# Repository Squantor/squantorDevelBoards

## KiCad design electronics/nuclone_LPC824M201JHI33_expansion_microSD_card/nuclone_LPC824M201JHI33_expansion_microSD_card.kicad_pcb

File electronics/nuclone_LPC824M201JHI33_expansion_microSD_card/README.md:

# LPC824M201JHI33 nuclone shrunk expansion board with micro SD card socket
Small nuclone expansion board for the [LPC824 nuclone](https://github.com/Squantor/squantorDevelBoards/tree/master/hardware/nuclone_LPC824M201JHI33/README.md) with a micro SD card socket and a 4 pin JST connection for hooking up an UART. The goal of this board to play around with a SD card driver not using SPI mode. Will focus first on single data line SD and later on switching to two and four dataline SD.
## Debug connector
There is a connector present to hook up a logic analyser for checking the signals.
# HSI (Hardware Software Interface)
This applies to a project that has a embedded software component. Describe what each pin/bus does, what it is connected to, what its function is and some "safe" behaviour when starting up.
* LPC824 PIO24 is connected to UART TX via 100Ohm series resistor
* LPC824 PIO25 is connected to UART RX via 100Ohm series resistor
* LPC824 PIO12 is connected to LED0 via 4.7KOhm resistor, this is used as alive blinky indicator
* LPC824 PIO23 is connected to LED1 via 4.7KOhm resistor, this is used as an activity indicator
* TODO SD card connections
## TODO's
Still some things need to be done:
* schematic entry
* PCB layout
* Review with one night in between
* Produce at [OSHPARK](https://oshpark.com/)
* Assemble
* Test & characterise
* update Readme.md with pictures and BOM
## BOM
* Any 25 style 8 pin SOIC serial flash is suitable like the [Winbond W25X20CLSNIG](https://lcsc.com/product-detail/FLASH_Winbond-Elec-W25X20CLSNIG_C34591.html)

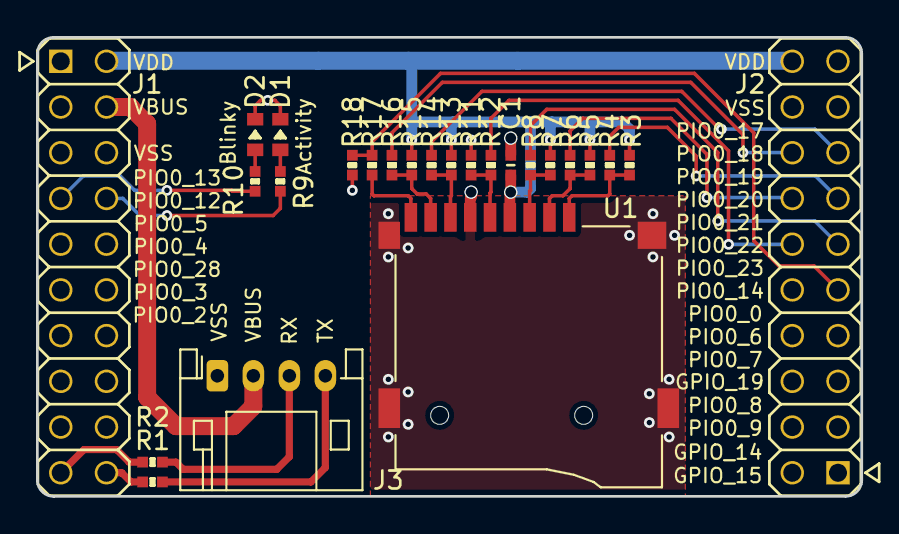
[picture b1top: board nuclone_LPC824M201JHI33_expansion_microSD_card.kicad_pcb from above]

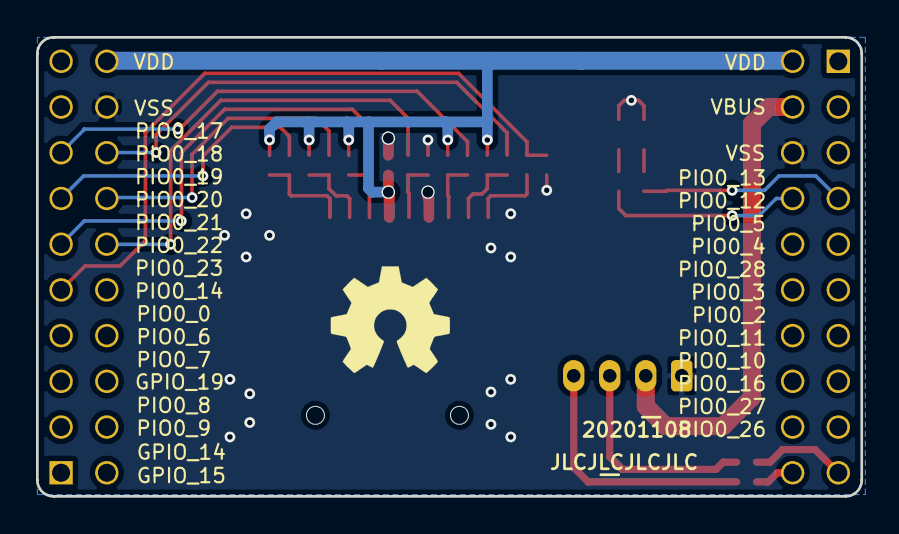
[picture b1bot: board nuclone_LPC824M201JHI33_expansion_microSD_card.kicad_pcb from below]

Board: 2 copper layers, 45.8 x 25.5 mm, 28 parts (3 on the bottom side), 25 nets.

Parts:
C1: 1u; C_0402
D1, D2: LED; LED_0603_hand
J1: nuclone_small_left; Header-0254-2X10-H010
J2: nuclone_small_right; Header-0254-2X10-H010
J3: DevBoardUartInput; JST_PH_S4B-PH-K_1x04_P2.00mm_Horizontal
N1: OHWLOGO; OSHW-Symbol_6.7x6mm_SilkScreen
N2: 20201108; Label_Generic
N3: JLCJLCJLCJLC; Label_Generic
R1, R2, R4, R6, R8, R12, R14, R16, R17: 100; R_0402_hand
R3, R5, R7, R11, R13, R15: 10k; R_0402_hand
R9, R10: 4.7K; R_0402_hand
R18: 100k; R_0402_hand
U1: microSD_socket; SDmicro_XUNPU_TF-115

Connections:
/CLK: J2.12, R12.2
/CMD: J2.11, R8.2
/CardDet: J2.9, R17.2, R18.2
/DAT0: J2.15, R14.2
/DAT1: J2.16, R16.2
/DAT2: J2.13, R4.2
/DAT3: J2.14, R6.2
/LED0: J1.8, R9.2
/LED1: J1.7, R10.2
/UART_RX: J1.19, R1.1
/UART_TX: J1.20, R2.1
/VBUS: J1.4, J3.2
/VDD: C1.1, J1.1, J1.2, J2.20, R3.2, R5.2, R7.2, R13.2, R15.2, U1.4
/VSS: C1.2, D1.1, D2.1, J1.6, J2.18, J3.1, R11.2, R18.1, U1.6, U1.S
unnamed: D1.2, R9.1
unnamed: D2.2, R10.1
unnamed: J3.3, R1.2
unnamed: J3.4, R2.2
unnamed: R3.1, R4.1, U1.1
unnamed: R5.1, R6.1, U1.2
unnamed: R7.1, R8.1, U1.3
unnamed: R11.1, R12.1, U1.5
unnamed: R13.1, R14.1, U1.7
unnamed: R15.1, R16.1, U1.8
unnamed: R17.1, U1.CD

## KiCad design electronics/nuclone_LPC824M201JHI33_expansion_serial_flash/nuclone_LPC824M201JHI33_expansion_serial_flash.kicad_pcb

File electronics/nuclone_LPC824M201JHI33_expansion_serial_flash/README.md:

# LPC824M201JHI33 nuclone shrunk expansion board with serial flash
Small nuclone expansion board for the [LPC824 nuclone](https://github.com/Squantor/squantorDevelBoards/tree/master/hardware/nuclone_LPC824M201JHI33/README.md) that also has a serial flash and a 4 pin JST connection for hooking up an UART. The goal of this board to play around with efficient serial flash handling, SPI drivers and filesystem driver development. Lets see if we can wring some performance out of it with QSPI.
# HSI (Hardware Software Interface)
This applies to a project that has a embedded software component. Describe what each pin/bus does, what it is connected to, what its function is and some "safe" behaviour when starting up.
* UART connection
* SPI connection
* blinking led for alive?
## TODO's
Still some things need to be done:
* schematic entry 
* PCB layout
* Review with one night in between
* Produce at [OSHPARK](https://oshpark.com/)
* Assemble
* Test & characterise
* update Readme.md with pictures and BOM
## BOM
* Any 25 style 8 pin SOIC serial flash is suitable like the [Winbond W25X20CLSNIG](https://lcsc.com/product-detail/FLASH_Winbond-Elec-W25X20CLSNIG_C34591.html)

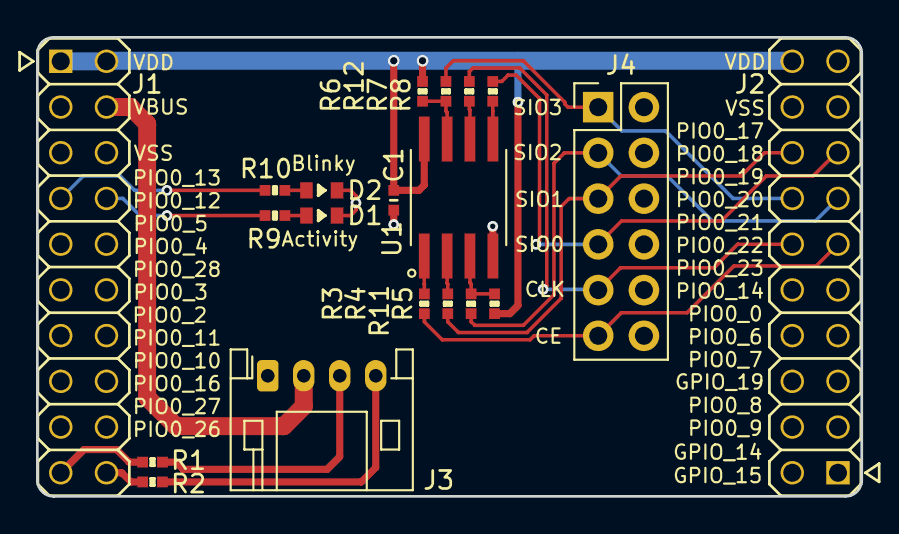
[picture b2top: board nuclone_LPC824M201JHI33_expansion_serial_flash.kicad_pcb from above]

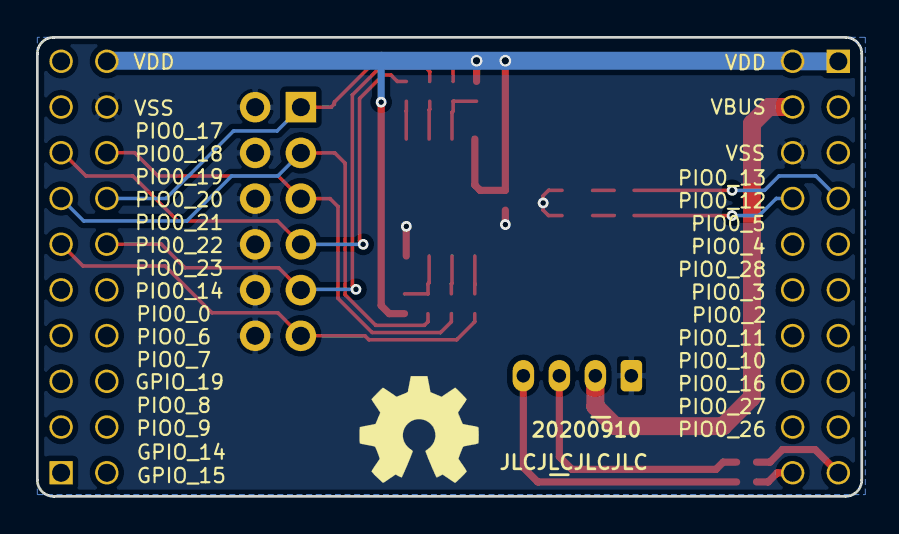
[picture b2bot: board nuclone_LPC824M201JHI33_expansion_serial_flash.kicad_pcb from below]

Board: 2 copper layers, 45.8 x 25.5 mm, 23 parts (3 on the bottom side), 23 nets.

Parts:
C1: 1u; C_0402
D1, D2: LED; LED_0603_hand
J1: nuclone_small_left; Header-0254-2X10-H010
J2: nuclone_small_right; Header-0254-2X10-H010
J3: DevBoardUartInput; JST_PH_S4B-PH-K_1x04_P2.00mm_Horizontal
J4: Conn_02x06_Odd_Even; PinHeader_2x06_P2.54mm_Vertical
N1: OHWLOGO; OSHW-Symbol_6.7x6mm_SilkScreen
N2: 20200910; Label_Generic
N3: JLCJLCJLCJLC; Label_Generic
R1, R2, R3, R4, R7, R8, R11, R12: 100; R_0402_hand
R5, R6: 10k; R_0402_hand
R9, R10: 4.7K; R_0402_hand
U1: generic 25XNN serial flash; SOIC-8_dual_wide

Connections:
/CE_FLASH: J2.11, J4.11, R3.2
/CLK: J2.12, J4.9, R7.1
/LED0: J1.8, R9.2
/LED1: J1.7, R10.2
/SIO0: J2.15, J4.7, R8.1
/SIO1: J2.16, J4.5, R4.2
/SIO2: J2.13, J4.3, R11.2
/SIO3: J2.14, J4.1, R12.1
/UART_RX: J1.19, R1.1
/UART_TX: J1.20, R2.1
/VBUS: J1.4, J3.2
/VDD: C1.1, J1.1, J1.2, J2.20, R5.2, R6.1, U1.8
/VSS: C1.2, D1.1, D2.1, J1.6, J2.18, J3.1, J4.2, J4.4, J4.6, J4.8, J4.10, J4.12, U1.4
unnamed: D1.2, R9.1
unnamed: D2.2, R10.1
unnamed: J3.3, R1.2
unnamed: J3.4, R2.2
unnamed: R3.1, U1.1
unnamed: R4.1, U1.2
unnamed: R7.2, U1.6
unnamed: R8.2, U1.5
unnamed: R5.1, R11.1, U1.3
unnamed: R6.2, R12.2, U1.7

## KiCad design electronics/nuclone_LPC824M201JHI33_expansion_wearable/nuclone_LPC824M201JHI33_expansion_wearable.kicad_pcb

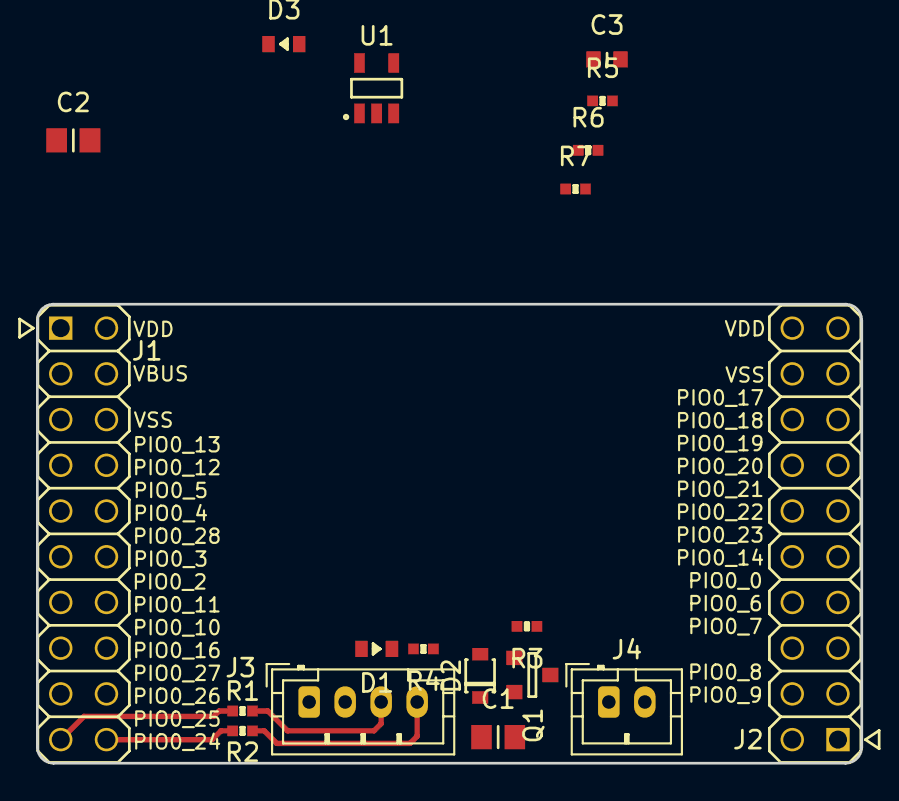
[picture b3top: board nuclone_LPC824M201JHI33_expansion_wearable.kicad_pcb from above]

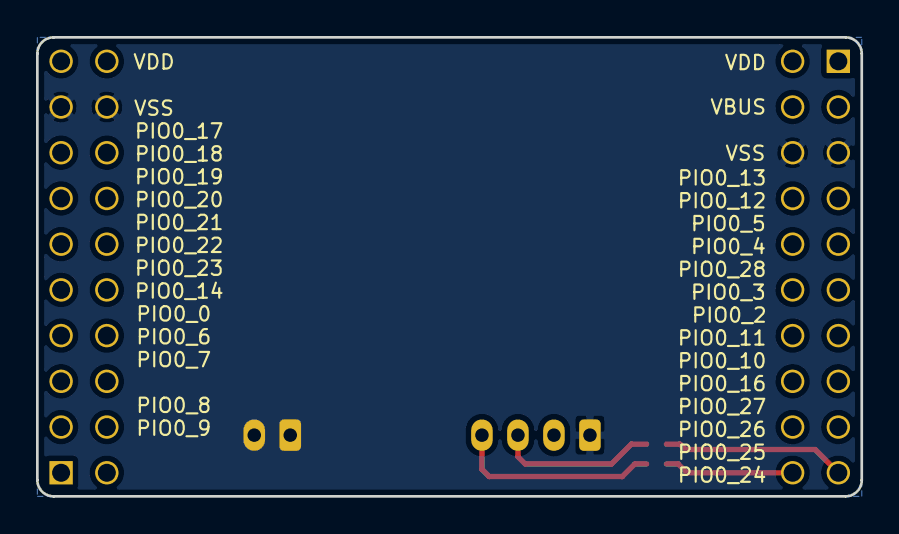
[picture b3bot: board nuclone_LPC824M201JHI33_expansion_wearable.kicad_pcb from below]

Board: 2 copper layers, 45.8 x 25.5 mm, 22 parts (3 on the bottom side), 13 nets.

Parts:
C1, C2: 10u; C_0805+0603
C3: 1u; C_0603
D1: GRN; LED_0603_hand
D2: NSR0320; SOD_323_onsemi
D3: RED; LED_0603_hand
J1: nuclone_small_left; Header-0254-2X10-H010
J2: nuclone_small_right; Header-0254-2X10-H010
J3: DevBoardUartInput; JST_PH_B4B-PH-K_1x04_P2.00mm_Vertical
J4: batt_recharge; JST_PH_B2B-PH-K_1x02_P2.00mm_Vertical
N1: OHWLOGO; OSHW-Symbol_6.7x6mm_SilkScreen
N2: 20200910; Label_Generic
N3: JLCJLCJLCJLC; Label_Generic
Q1: DMG2305; SOT23-3
R1, R2: 100; R_0402_hand
R3: 100K; R_0402_hand
R4, R6: 1K; R_0402_hand
R5: 22K; R_0402_hand
R7: 47K; R_0402_hand
U1: MCP738312-OT; SOT23-5-Microchip-OT

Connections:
/PIO0_24: J1.20, R2.1
/PIO0_25: J1.19, R1.1
/VBAT: C2.1, J4.1, Q1.3, U1.3
/VBUS: C1.1, D2.1, J1.3, J1.4, Q1.2
/VDD: J1.1, J1.2, J2.19, J2.20, R7.2
/VSS: C1.2, C2.2, C3.1, J1.5, J1.6, J2.17, J2.18, J3.1, J4.2, R3.1, R4.1, R5.2, U1.2
/VUSB: C3.2, D1.2, D2.2, D3.2, J3.2, Q1.1, R3.2, U1.4
/chrg_en: R5.1, U1.5
/chrg_state: R6.1, R7.1, U1.1
unnamed: D1.1, R4.2
unnamed: D3.1, R6.2
unnamed: J3.3, R1.2
unnamed: J3.4, R2.2

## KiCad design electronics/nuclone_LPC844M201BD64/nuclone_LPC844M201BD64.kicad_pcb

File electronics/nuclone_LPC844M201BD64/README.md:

# Nuclone development board for the LPC84XM201BD64
Development board for the LPC844 and LPC845 in TQFP64 package.
# HSI (Hardware Software Interface)
* TODO pins
* The crystal is a 12MHz 3225 type
* VREFP is connected to VDDA via default closed jumper labeled VREFP
* VREFN is connected to VSSA via default closed jumper labeled VREFN
## TODO's
Still some things need to be done:
* Schematic
* Layout
* review with one night in between
* Produce at [OSHPARK](https://oshpark.com/)
* Assemble
* Test & characterise
* update Readme.md with pictures and BOM
## BOM

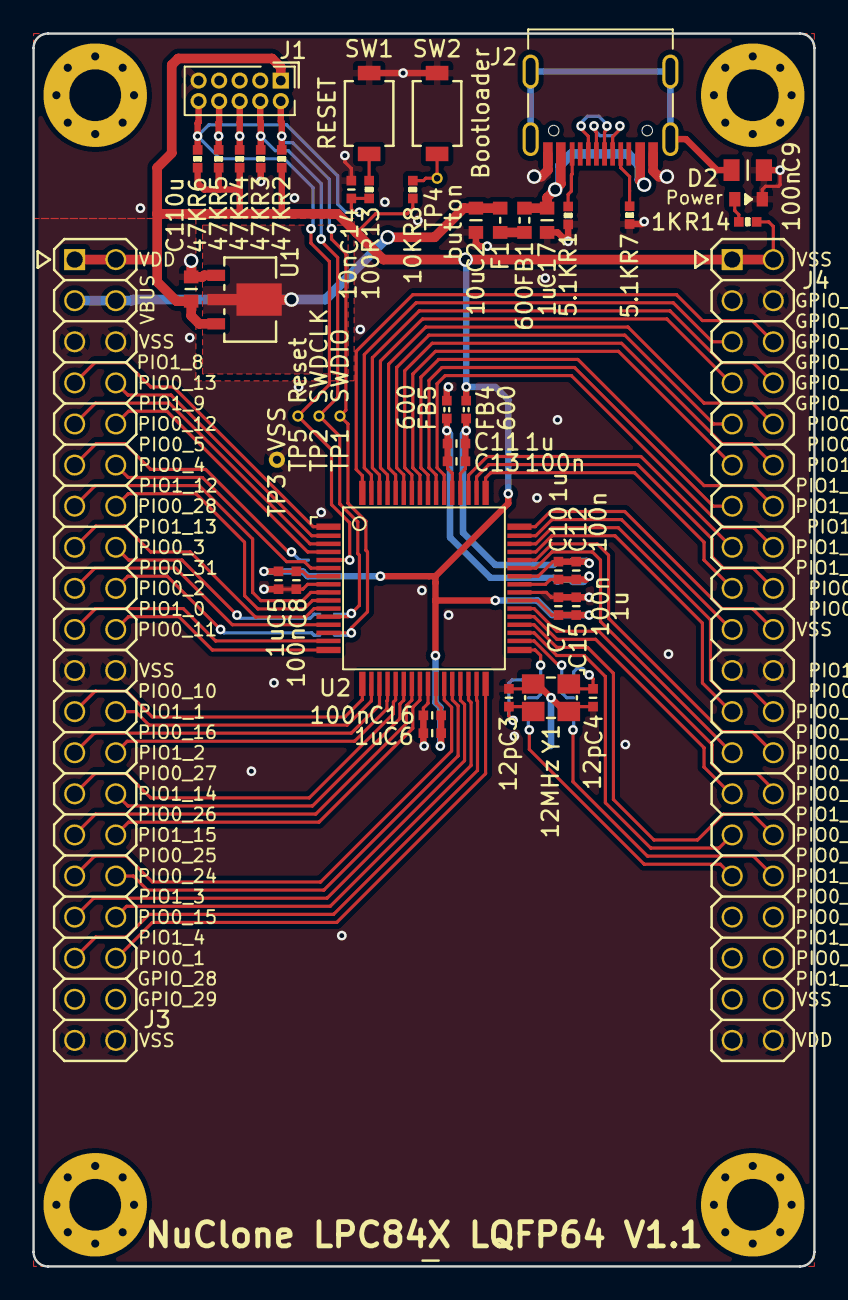
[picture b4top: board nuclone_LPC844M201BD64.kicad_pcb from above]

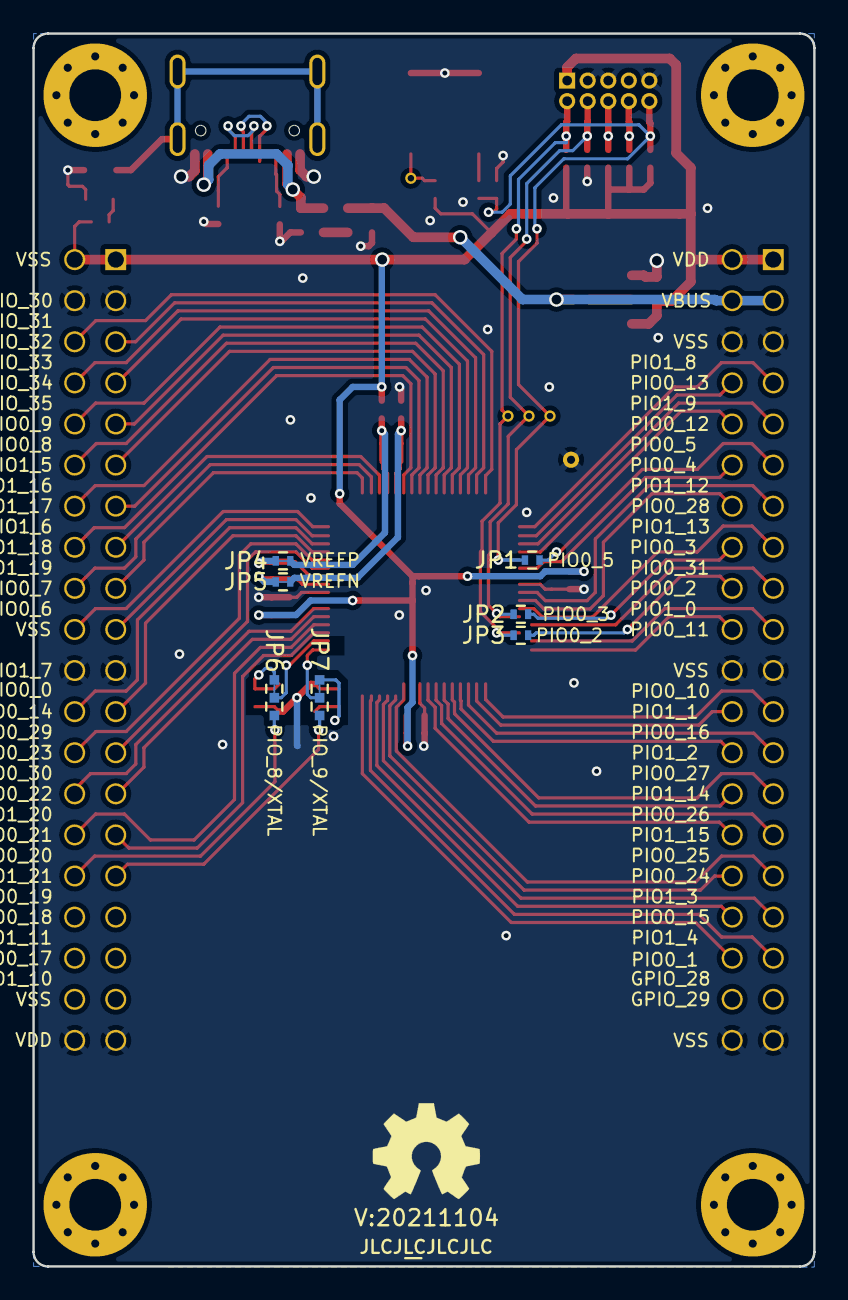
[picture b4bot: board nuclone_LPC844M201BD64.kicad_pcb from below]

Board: 2 copper layers, 48.3 x 76.2 mm, 61 parts (10 on the bottom side), 80 nets.

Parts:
C1, C2: 10u; C_0603
C3, C4: 12p; C_0402
C5, C6, C10, C11, C15: 1u; C_0402
C7, C8, C12, C13, C16: 100n; C_0402
C9: 100n; C_0805
C14: 10n; C_0402
C17: 1u; C_0603
D2: GREEN; LED_0603_hand
F1: 0.5A; F_0603_hand
FB1: 600; L_0603
FB4, FB5: 600; L_0402
H1, H2, H3, H4: MountingHole; MountingHole_3.2mm_M3_Pad_Via
J1: JTAG_2X05; Header-0127-2X05-H006
J2: TYPE-C-31-M-12; USB-C-HRO-31-M-12
J3: nuclone_small_left; nuclone_medium_left
J4: nuclone_small_right; nuclone_medium_right
JP1: PIO0_5; solder_jumper_2way_noconn
JP2: PIO0_3; solder_jumper_2way_noconn
JP3: PIO0_2; solder_jumper_2way_noconn
JP4: VREFP; solder_jumper_2way_conn
JP5: VREFN; solder_jumper_2way_conn
JP6: PIO_8/XTAL; solder_jumper_3way_12conn
JP7: PIO_9/XTAL; solder_jumper_3way_12conn
N1: OHWLOGO; OSHW-Symbol_6.7x6mm_SilkScreen
N2: 20211104; Label_version
N3: JLCJLCJLCJLC; Label_Generic
N4: NuClone LPC84X LQFP64 V1.1; Label_Generic
R1, R7: 5.1K; R_0402_hand
R2, R3, R4, R5, R6: 47K; R_0402_hand
R8: 10K; R_0402_hand
R13: 100; R_0402_hand
R14: 1K; R_0402_hand
SW1: RESET; TD-85XU
SW2: Bootloader; TD-85XU
TP1: SWDIO; TestPoint_hole_H04R07
TP2: SWDCLK; TestPoint_hole_H04R07
TP3: VSS; TestPoint_hole_H05R10
TP4: button; TestPoint_hole_H04R07
TP5: Reset; TestPoint_hole_H04R07
U1: MCP1702-MB; SOT89-NXP
U2: LPC845M301BD64; SOT314-2
Y1: 12MHz; Crystal_3225_4

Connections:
/Bootloader: R8.1, SW2.2, TP4.1
/PIO0_0: J4.20 (VSS), U2.48 (PIO0_0/ACMP_I1/TDO)
/PIO0_1: J3.36 (GPIO_27), U2.32 (PIO0_1/ACMP_I2/CLKIN/TDI)
/PIO0_2: J3.18 (GPIO_11), JP3.1
/PIO0_3: J3.16 (GPIO_09), JP2.1
/PIO0_4: J3.12 (GPIO_05), U2.6 (PIO0_4/ADC_11/TRSTN/WAKEUP)
/PIO0_5: J3.11 (GPIO_04), JP1.1
/PIO0_6: J4.24 (GPIO_48), U2.46 (PIO0_6/ADC_1/ACMPVREF)
/PIO0_7: J4.23 (GPIO_49), U2.45 (PIO0_7/ADC_0)
/PIO0_8: J4.32 (GPIO_56), JP6.3
/PIO0_8_I: JP6.2, U2.34 (PIO0_8/XTALIN)
/PIO0_9: J4.31 (GPIO_57), JP7.3
/PIO0_9_I: JP7.2, U2.33 (PIO0_9/XTALOUT)
/PIO0_10: J3.23 (GPIO_14), U2.17 (PIO0_10/I2C0_SCL_)
/PIO0_11: J3.20 (GPIO_13), U2.16 (PIO0_11/I2C0_SDA)
/PIO0_12: J3.10 (GPIO_03), U2.4 (PIO0_12)
/PIO0_13: J3.8 (GPIO_01), U2.2 (PIO0_13/ADC_10)
/PIO0_14: J4.17 (GPIO_45), U2.49 (PIO0_14/ACMP_I3/ADC_2)
/PIO0_15: J3.34 (GPIO_25), U2.30 (PIO0_15)
/PIO0_16: J3.25 (GPIO_16), U2.19 (PIO0_16)
/PIO0_17: J4.5 (GPIO_33), U2.63 (PIO0_17/ADC_9/DACOUT_0)
/PIO0_18: J4.7 (GPIO_35), U2.61 (PIO0_18/ADC_8)
/PIO0_19: J4.10 (GPIO_36), U2.60 (PIO0_19/ADC_7)
/PIO0_20: J4.12 (GPIO_38), U2.58 (PIO0_20/ADC_6)
/PIO0_21: J4.11 (GPIO_39), U2.57 (PIO0_21/ADC_5)
/PIO0_22: J4.13 (GPIO_41), U2.55 (PIO0_22/ADC_4)
/PIO0_23: J4.15 (GPIO_43), U2.51 (PIO0_23/ADC_3/ACMP_I4)
/PIO0_24: J3.32 (GPIO_23), U2.28 (PIO0_24)
/PIO0_25: J3.31 (GPIO_22), U2.27 (PIO0_25)
/PIO0_26: J3.29 (GPIO_20), U2.23 (PIO0_26)
/PIO0_27: J3.27 (GPIO_18), U2.21 (PIO0_27)
/PIO0_28: J3.14 (GPIO_07), U2.10 (PIO0_28/WKTCLKIN)
/PIO0_29: J4.18 (GPIO_44), U2.50 (PIO0_29/_DACOUT_1)
/PIO0_30: J4.16 (GPIO_42), U2.54 (PIO0_30/ACMP_I5)
/PIO0_31: J3.17 (GPIO_10), U2.13 (PIO0_31/CAPT_X0)
/PIO1_0: J3.19 (GPIO_12), U2.15 (PIO1_0/CAPT_X1)
/PIO1_1: J3.24 (GPIO_15), U2.18 (PIO1_1/CAPT_X2)
/PIO1_2: J3.26 (GPIO_17), U2.20 (PIO1_2/CAPT_X3)
/PIO1_3: J3.33 (GPIO_24), U2.29 (PIO1_3/CAPT_X4)
/PIO1_4: J3.35 (GPIO_26), U2.31 (PIO1_4/CAPT_X5)
/PIO1_5: J4.29 (GPIO_55), U2.35 (PIO1_5/CAPT_X6)
/PIO1_6: J4.28 (GPIO_52), U2.38 (PIO1_6/CAPT_X7)
/PIO1_7: J4.19 (VSS), U2.47 (PIO1_7/CAPT_X8)
/PIO1_8: J3.7 (GPIO_00), U2.1 (PIO1_8/CAPT_YL)
/PIO1_9: J3.9 (GPIO_02), U2.3 (PIO1_9/CAPT_YH)
/PIO1_10: J4.6 (GPIO_32), U2.64 (PIO1_10)
/PIO1_11: J4.8 (GPIO_34), U2.62 (PIO1_11)
/PIO1_12: J3.13 (GPIO_06), U2.9 (PIO1_12)
/PIO1_13: J3.15 (GPIO_08), U2.11 (PIO1_13)
/PIO1_14: J3.28 (GPIO_19), U2.22 (PIO1_14)
/PIO1_15: J3.30 (GPIO_21), U2.24 (PIO1_15)
/PIO1_16: J4.30 (GPIO_54), U2.36 (PIO1_16)
/PIO1_17: J4.27 (GPIO_53), U2.37 (PIO1_17)
/PIO1_18: J4.25 (GPIO_51), U2.43 (PIO1_18)
/PIO1_19: J4.26 (GPIO_50), U2.44 (PIO1_19)
/PIO1_20: J4.14 (GPIO_40), U2.56 (PIO1_20)
/PIO1_21: J4.9 (GPIO_37), U2.59 (PIO1_21)
/RESET: C14.2, J1.10 (nRESET), JP1.2, R6.1, R13.1, TP5.1, U2.5 (RESET/PIO0_5)
/TCK: J1.4 (SWDCLK/TCK), JP2.2, R3.1, TP2.1, U2.12 (SWCLK/PIO0_3/TCK)
/TDI: J1.8 (TDI), R5.1
/TDO: J1.6 (SWO/TDO), R4.1
/TMS: J1.2 (SWDIO/TMS), JP3.2, R2.1, TP1.1, U2.14 (SWDIO/PIO0_2/TMS)
/VBUS: C2.2, F1.1, J3.3 (VBUS), J3.4 (VBUS), U1.2 (Vin)
/VDD: C1.1, C5.1, C6.1, C7.1, C8.1, C15.1, C16.1, FB4.2, J1.1 (VCC), J3.1 (VDD), J3.2 (VDD), J4.1 (VSS), J4.2 (VSS), R2.2, R4.2, R5.2, R6.2, R8.2, R14.2, U1.3 (Vout), U2.7 (VDD), U2.26 (VDD), U2.39 (VDD)
/VDDA: C11.1, C13.1, FB4.1, JP4.1, U2.52 (VDDA)
/VREFN: C10.2, C12.2, JP5.2, U2.41 (VREFN)
/VREFP: C10.1, C12.1, JP4.2, U2.42 (VREFP)
/VSS: C1.2, C2.1, C3.2, C4.2, C5.2, C6.2, C7.2, C8.2, C9.1, C14.1, C15.2, C16.2, C17.1, D2.1 (K), FB5.2, J1.3 (GND), J1.5 (GND), J1.9 (GNDDET), J2.A1B12 (GND), J2.B1A12 (GND), J3.5 (VSS), J3.6 (VSS), J3.21 (VSS), J3.22 (VSS), J3.39 (VSS), J3.40 (VSS), J4.3 (GPIO_31), J4.4 (GPIO_30), J4.21 (GPIO_47), J4.22 (GPIO_46), J4.39 (VDD), J4.40 (VDD), R1.1, R3.2, R7.1, SW1.1, SW2.1, TP3.1, U1.1 (GND), U2.8 (VSS), U2.25 (VSS), U2.40 (VSS), Y1.2, Y1.4
/VSSA: C11.2, C13.2, FB5.1, JP5.1, U2.53 (VSSA)
/XTALIN: C4.1, JP6.1, Y1.1
/XTALOUT: C3.1, JP7.1, Y1.3
unnamed: C9.2, J2.S (Shield)
unnamed: C17.2, FB1.2, J2.A4B9 (VBUS), J2.B4A9 (VBUS)
unnamed: D2.2 (A), R14.1
unnamed: F1.2, FB1.1
unnamed: J2.A5 (CC1), R7.2
unnamed: J2.A6 (DP1), J2.B6 (DP2)
unnamed: J2.A7 (DN1), J2.B7 (DN2)
unnamed: J2.B5 (CC2), R1.2
unnamed: R13.2, SW1.2

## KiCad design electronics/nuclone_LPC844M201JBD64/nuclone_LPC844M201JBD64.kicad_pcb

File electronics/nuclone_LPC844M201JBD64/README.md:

# Nuclone development board for the LPC844M201JBD64
Development board for the LPC844 in PQFP64 package.
# HSI (Hardware Software Interface)
* TODO pins
* The crystal is a 12MHz 3225 type
* VREFP is connected to VDDA via default closed jumper labeled VREFP
* VREFN is connected to VSSA via default closed jumper labeled VREFN
## TODO's
Still some things need to be done:
* Schematic
* Layout
* review with one night in between
* Produce at [OSHPARK](https://oshpark.com/)
* Assemble
* Test & characterise
* update Readme.md with pictures and BOM
## BOM

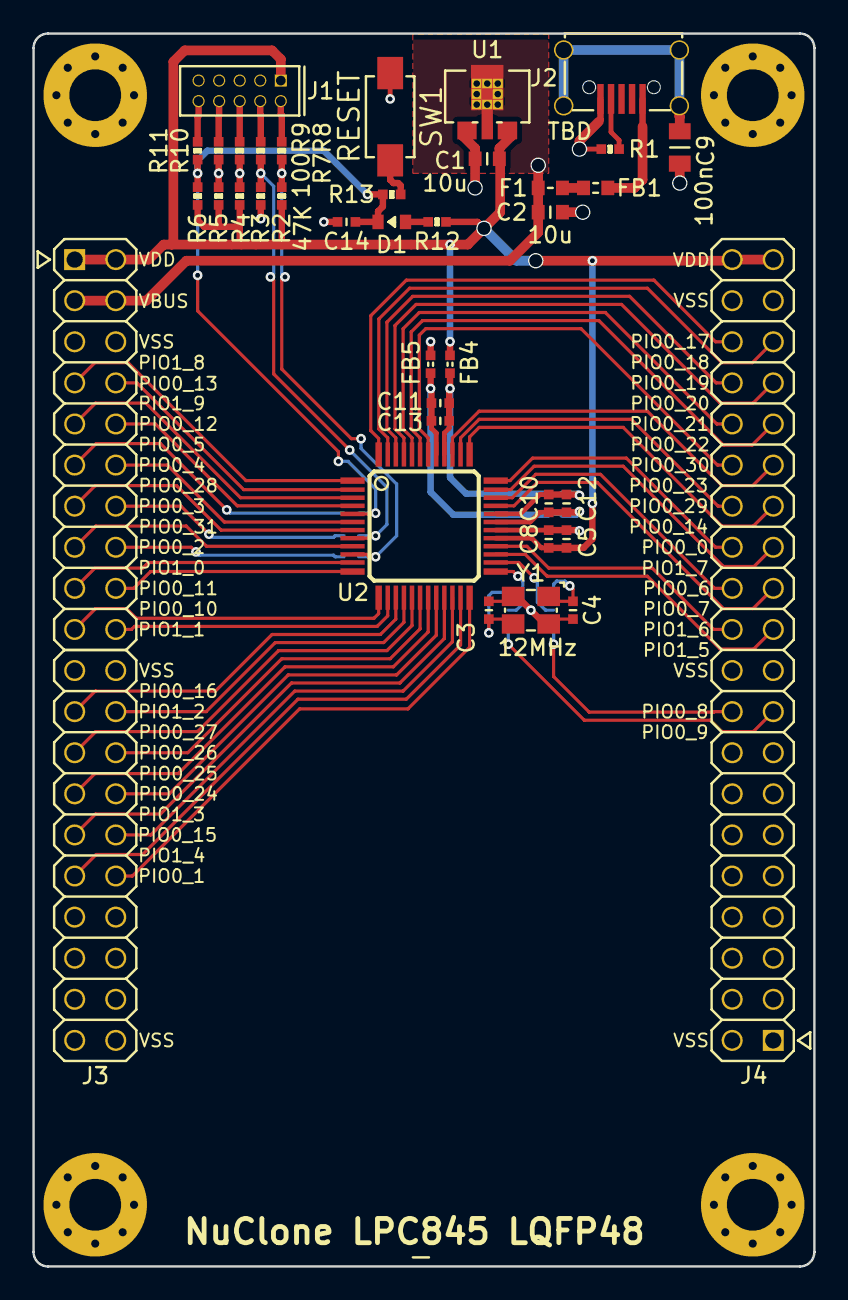
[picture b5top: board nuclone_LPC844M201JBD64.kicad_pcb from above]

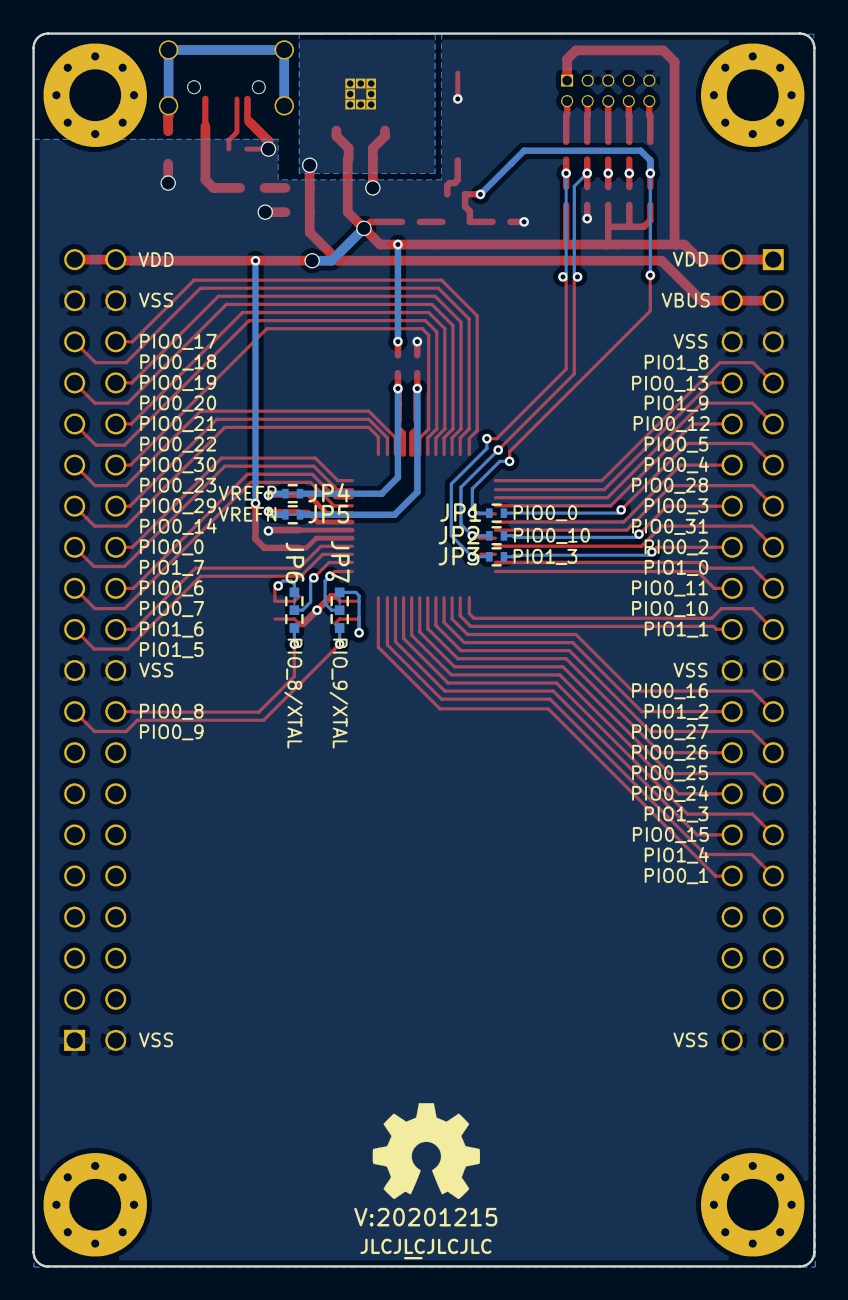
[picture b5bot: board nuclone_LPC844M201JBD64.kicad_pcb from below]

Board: 2 copper layers, 48.3 x 76.2 mm, 53 parts (10 on the bottom side), 69 nets.

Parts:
C1, C2: 10u; C_0603
C3, C4: 12p; C_0402
C5, C10, C11: 1u; C_0402
C8, C12, C13: 100n; C_0402
C9: 100n; C_0805
C14: 10n; C_0402
D1: RED; LED_0603_hand
F1: 0.5A; F_0603_hand
FB1: 100; L_0603
FB4, FB5: 600; L_0402
H1, H2, H3, H4: MountingHole; MountingHole_3.2mm_M3_Pad_Via
J1: JTAG_2X05; Header-0127-2X05-H006
J2: USB-ID; USB-muB-SMD_TH
J3: nuclone_small_left; nuclone_medium_left
J4: nuclone_small_right; nuclone_medium_right
JP1: PIO0_0; solder_jumper_2way_noconn
JP2: PIO0_10; solder_jumper_2way_noconn
JP3: PIO1_3; solder_jumper_2way_noconn
JP4: VREFP; solder_jumper_2way_conn
JP5: VREFN; solder_jumper_2way_conn
JP6: PIO_8/XTAL; solder_jumper_3way_12conn
JP7: PIO_9/XTAL; solder_jumper_3way_12conn
N1: OHWLOGO; OSHW-Symbol_6.7x6mm_SilkScreen
N2: 20201215; Label_version
N3: JLCJLCJLCJLC; Label_Generic
N4: NuClone LPC845 LQFP48; Label_Generic
R1: TBD; R_0402_hand
R2, R3, R4, R5, R6: 47K; R_0402_hand
R7, R8, R9, R10, R11, R13: 100; R_0402_hand
R12: 10K; R_0402_hand
SW1: RESET; DTSM3
U1: MCP1702-MB; SOT89-SOT23-Dual-NXP
U2: LPC845M301JBD48; SOT313-2-NXP
Y1: 12MHz; Crystal_3225_4

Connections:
/PIO0_0: J4.26, U2.36
/PIO0_1: J3.32, U2.24
/PIO0_2: J3.16, JP3.1
/PIO0_3: J3.14, JP2.1
/PIO0_4: J3.12, U2.6
/PIO0_5: J3.11, JP1.1
/PIO0_6: J4.24, U2.34
/PIO0_7: J4.23, U2.33
/PIO0_8: J4.18, JP6.3
/PIO0_8_I: JP6.2, U2.26
/PIO0_9: J4.17, JP7.3
/PIO0_9_I: JP7.2, U2.25
/PIO0_10: J3.19, U2.13
/PIO0_11: J3.18, U2.12
/PIO0_12: J3.10, U2.4
/PIO0_13: J3.8, U2.2
/PIO0_14: J4.27, U2.37
/PIO0_15: J3.30, U2.22
/PIO0_16: J3.23, U2.15
/PIO0_17: J4.36, U2.48
/PIO0_18: J4.35, U2.47
/PIO0_19: J4.34, U2.46
/PIO0_20: J4.33, U2.45
/PIO0_21: J4.32, U2.44
/PIO0_22: J4.31, U2.43
/PIO0_23: J4.29, U2.39
/PIO0_24: J3.28, U2.20
/PIO0_25: J3.27, U2.19
/PIO0_26: J3.26, U2.18
/PIO0_27: J3.25, U2.17
/PIO0_28: J3.13, U2.7
/PIO0_29: J4.28, U2.38
/PIO0_30: J4.30, U2.42
/PIO0_31: J3.15, U2.9
/PIO1_0: J3.17, U2.11
/PIO1_1: J3.20, U2.14
/PIO1_2: J3.24, U2.16
/PIO1_3: J3.29, U2.21
/PIO1_4: J3.31, U2.23
/PIO1_5: J4.21, U2.27
/PIO1_6: J4.22, U2.28
/PIO1_7: J4.25, U2.35
/PIO1_8: J3.7, U2.1
/PIO1_9: J3.9, U2.3
/RESET: C14.2, D1.1, JP1.2, R6.1, R11.2, R13.1, U2.5
/TCK: JP2.2, R3.1, R8.2, U2.8
/TDI: R5.1, R10.2
/TDO: R4.1, R9.2
/TMS: JP3.2, R2.1, R7.2, U2.10
/VBUS: C2.2, F1.1, J3.3, J3.4, U1.2
/VDD: C1.1, C5.1, C8.1, FB4.2, J1.1, J3.1, J3.2, J4.39, J4.40, R2.2, R4.2, R5.2, R6.2, R12.2, U1.3, U2.29
/VDDA: C11.1, C13.1, FB4.1, JP4.1, U2.40
/VREFN: C10.2, C12.2, JP5.2, U2.31
/VREFP: C10.1, C12.1, JP4.2, U2.32
/VSS: C1.2, C2.1, C3.2, C4.2, C5.2, C8.2, C9.1, C14.1, FB5.2, J1.3, J1.5, J1.9, J2.5, J3.5, J3.6, J3.21, J3.22, J3.39, J3.40, J4.1, J4.2, J4.19, J4.20, J4.37, J4.38, R1.1, R3.2, SW1.1, U1.1, U2.30, Y1.2, Y1.4
/VSSA: C11.2, C13.2, FB5.1, JP5.1, U2.41
/XTALIN: C4.1, JP6.1, Y1.1
/XTALOUT: C3.1, JP7.1, Y1.3
unnamed: C9.2, J2.S
unnamed: D1.2, R12.1
unnamed: F1.2, FB1.1
unnamed: FB1.2, J2.1
unnamed: J1.2, R7.1
unnamed: J1.4, R8.1
unnamed: J1.6, R9.1
unnamed: J1.8, R10.1
unnamed: J1.10, R11.1
unnamed: J2.4, R1.2
unnamed: R13.2, SW1.2
